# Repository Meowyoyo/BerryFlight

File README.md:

# BerryFlight
A UAV flight controller with advanced video and computing capabilities.

BerryFlight is a flight control board based on established BetaFlight / INAV Flight STM32 flifgt controllers. 

In addition to that it brings a RV1126 ARM Quadcore SoC, 2 GB of RAM and 8 GB of storage.
The on board Linux will propell you UAV into the next century =D

Running OpenHD with a USB Cam or use the two analog video inputs. 
Send the video digital over Wifibroadcast or analog via a normal 5.8 GHz VTX.

## The specs:
- STM32F722RET (BF/INAV/Ardu?) based flight controller
- 36x36mm 6-layer board, 30.5mm mounting holes
- ICM-20602 gyro
- BME280 baro
- Rockchip RV1126 ARM quadcore Cortex-A7 
- 2GB LPDDR3 RAM
- 8GB eMMC storage
- analog video out
- USB 2.0 and USB 3.0
- TVP5150AM1 analog video in IC, 2 channel
- AXP805 power management IC, 5 channel DC-DC, 10 channel LDO

## Contact:
Any additional functions needed?
Feel free to improve my design.
Open to any kind of input!

[Telegram Group](https://t.me/joinchat/x0q7eM5X5ahhNjhi)

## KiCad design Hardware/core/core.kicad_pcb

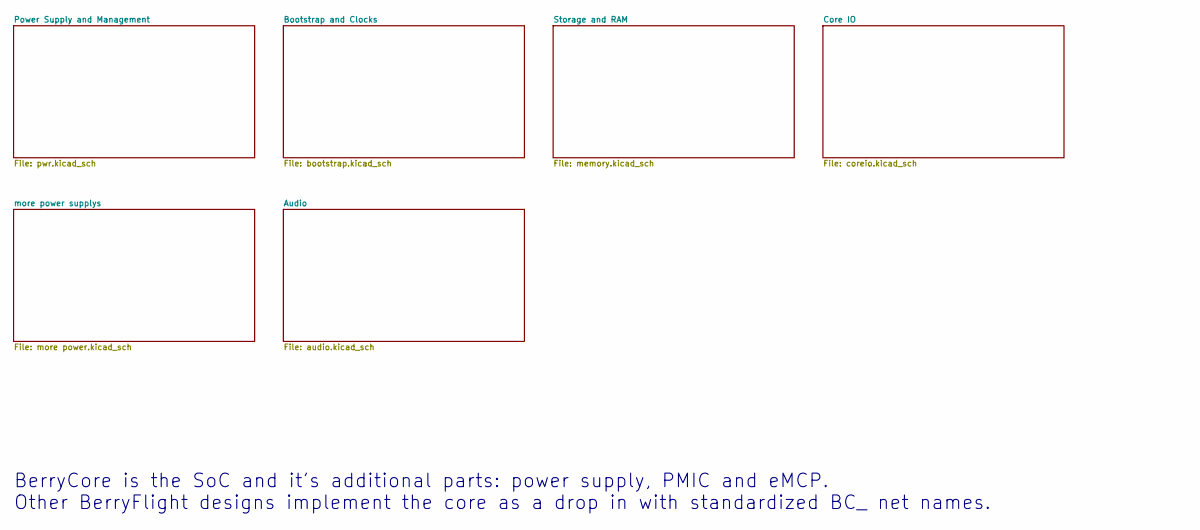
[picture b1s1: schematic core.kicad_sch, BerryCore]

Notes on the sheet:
BerryCore is the SoC and it's additional parts: power supply, PMIC and eMCP. Other BerryFlight designs implement the core as a drop in with standardized BC_ net names.

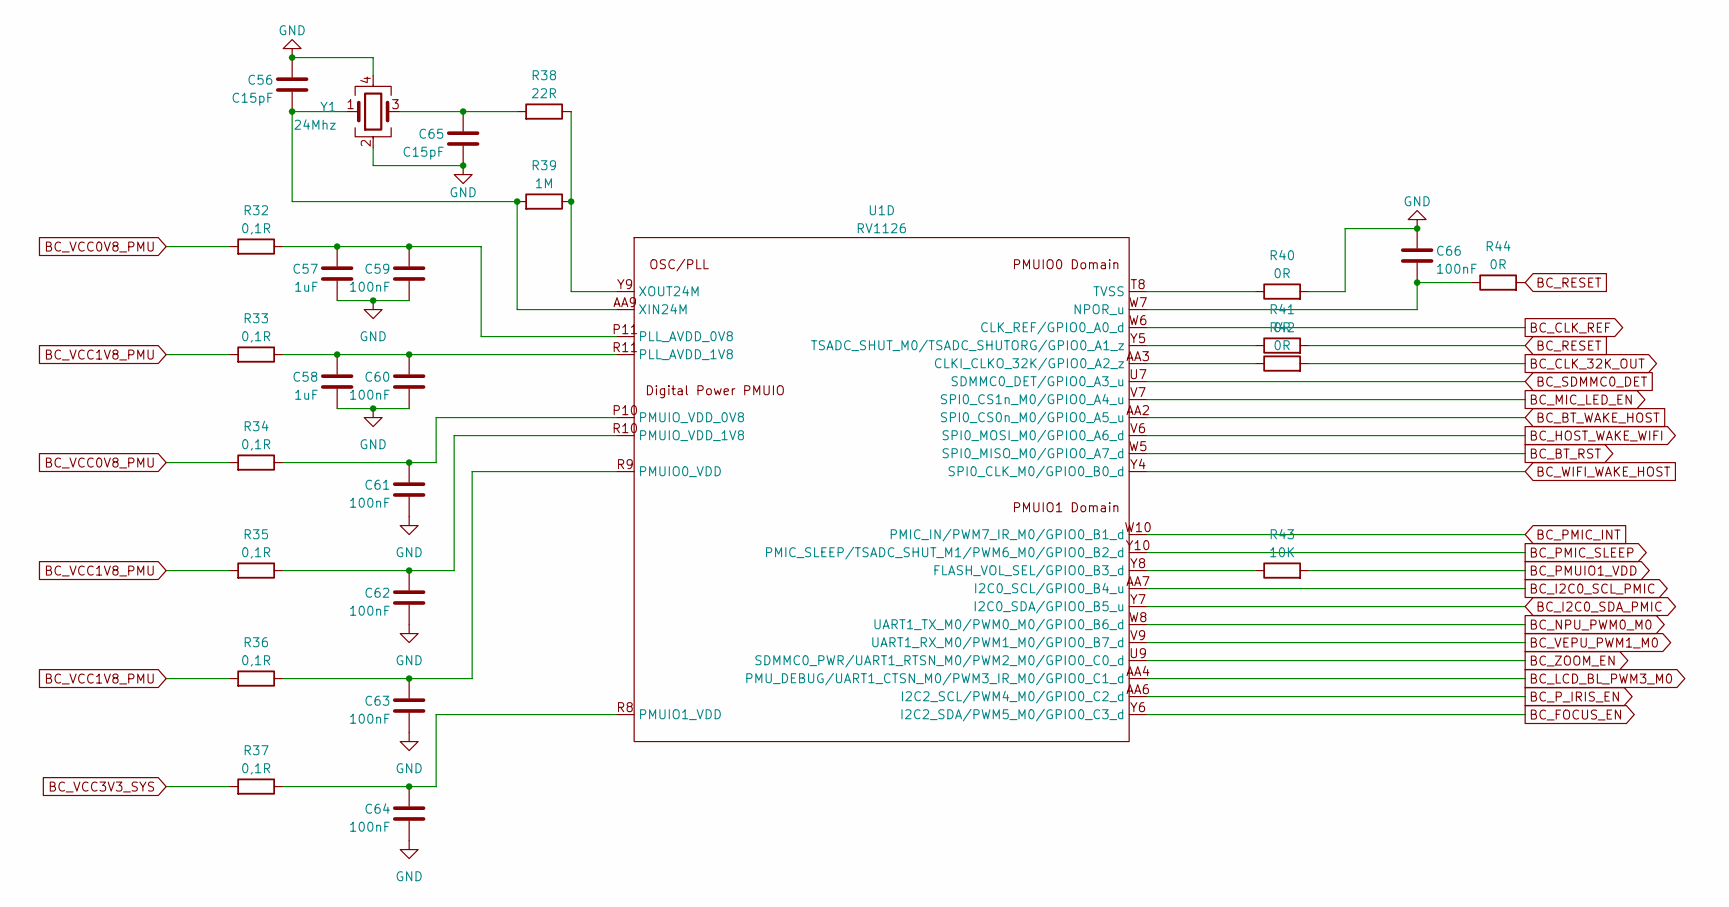
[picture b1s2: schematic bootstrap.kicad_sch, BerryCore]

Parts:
C56, C65: C15pF; C_0402_1005Metric
C57, C58: 1uF; C_0402_1005Metric
C59, C60, C61, C62, C63, C64: 100nF; C_0201_0603Metric
C66: 100nF; C_0402_1005Metric
R32, R33, R34, R35, R36, R37: 0,1R; R_0603_1608Metric
R38: 22R; R_0402_1005Metric
R39: 1M; R_0402_1005Metric
R40, R41, R42, R44: 0R; R_0402_1005Metric
R43: 10K; R_0402_1005Metric
U1: RV1126
Y1: 24Mhz; Oscillator_SMD_Abracon_ASE-4Pin_3.2x2.5mm

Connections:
BC_BT_RST: U1.W5 (SPI0_MISO_M0/GPIO0_A7_d)
BC_BT_WAKE_HOST: U1.AA2 (SPI0_CS0n_M0/GPIO0_A5_u)
BC_CLK_32K_OUT: R42.2; also elsewhere on the board
BC_CLK_REF: U1.W6 (CLK_REF/GPIO0_A0_d)
BC_FOCUS_EN: U1.Y6 (I2C2_SDA/PWM5_M0/GPIO0_C3_d)
BC_HOST_WAKE_WIFI: U1.V6 (SPI0_MOSI_M0/GPIO0_A6_d)
BC_I2C0_SCL_PMIC: U1.AA7 (I2C0_SCL/GPIO0_B4_u); also elsewhere on the board
BC_I2C0_SDA_PMIC: U1.Y7 (I2C0_SDA/GPIO0_B5_u); also elsewhere on the board
BC_LCD_BL_PWM3_M0: U1.AA4 (PMU_DEBUG/UART1_CTSN_M0/PWM3_IR_M0/GPIO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)
BC_MIC_LED_EN: U1.V7 (SPI0_CS1n_M0/GPIO0_A4_u)
BC_NPU_PWM0_M0: U1.W8 (UART1_TX_M0/PWM0_M0/GPIO0_B6_d); also elsewhere on the board
BC_PMIC_INT: U1.W10 (PMIC_IN/PWM7_IR_M0/GPIO0_B1_d); also elsewhere on the board
BC_PMIC_SLEEP: U1.Y10 (PMIC_SLEEP/TSADC_SHUT_M1/PWM6_M0/GPIO0_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); also elsewhere on the board
BC_PMUIO1_VDD: R43.2
BC_P_IRIS_EN: U1.AA6 (I2C2_SCL/PWM4_M0/GPIO0_C2_d)
BC_RESET: R41.2, R44.2; also elsewhere on the board
BC_SDMMC0_DET: U1.U7 (SDMMC0_DET/GPIO0_A3_u)
BC_VCC0V8_PMU: R32.2, R34.2; also elsewhere on the board
BC_VCC1V8_PMU: R33.2, R35.2, R36.2; also elsewhere on the board
BC_VCC3V3_SYS: R37.2; also elsewhere on the board
BC_VEPU_PWM1_M0: U1.V9 (UART1_RX_M0/PWM1_M0/GPIO0_B7_d)
BC_WIFI_WAKE_HOST: U1.Y4 (SPI0_CLK_M0/GPIO0_B0_d)
BC_ZOOM_EN: U1.U9 (SDMMC0_PWR/UART1_RTSN_M0/PWM2_M0/GPIO0_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)
GND: C56.1, C57.2, C58.2, C59.2, C60.2, C61.2, C62.2, C63.2, C64.2, C65.2, C66.1, R40.2, Y1.2, Y1.4; also elsewhere on the board
unnamed: C56.2, R39.2, U1.AA9 (XIN24M), Y1.1
unnamed: C57.1, C59.1, R32.1, U1.P11 (PLL_AVDD_0V8)
unnamed: C58.1, C60.1, R33.1, U1.R11 (PLL_AVDD_1V8)
unnamed: C61.1, R34.1, U1.P10 (PMUIO_VDD_0V8)
unnamed: C62.1, R35.1, U1.R10 (PMUIO_VDD_1V8)
unnamed: C63.1, R36.1, U1.R9 (PMUIO0_VDD)
unnamed: C64.1, R37.1, U1.R8 (PMUIO1_VDD)
unnamed: C65.1, R38.2, Y1.3
unnamed: C66.2, R44.1, U1.W7 (NPOR_u)
unnamed: R38.1, R39.1, U1.Y9 (XOUT24M)
unnamed: R40.1, U1.T8 (TVSS)
unnamed: R41.1, U1.Y5 (TSADC_SHUT_M0/TSADC_SHUTORG/GPIO0_A1_z)
unnamed: R42.1, U1.AA3 (CLKI_CLKO_32K/GPIO0_A2_z)
unnamed: R43.1, U1.Y8 (FLASH_VOL_SEL/GPIO0_B3_d)

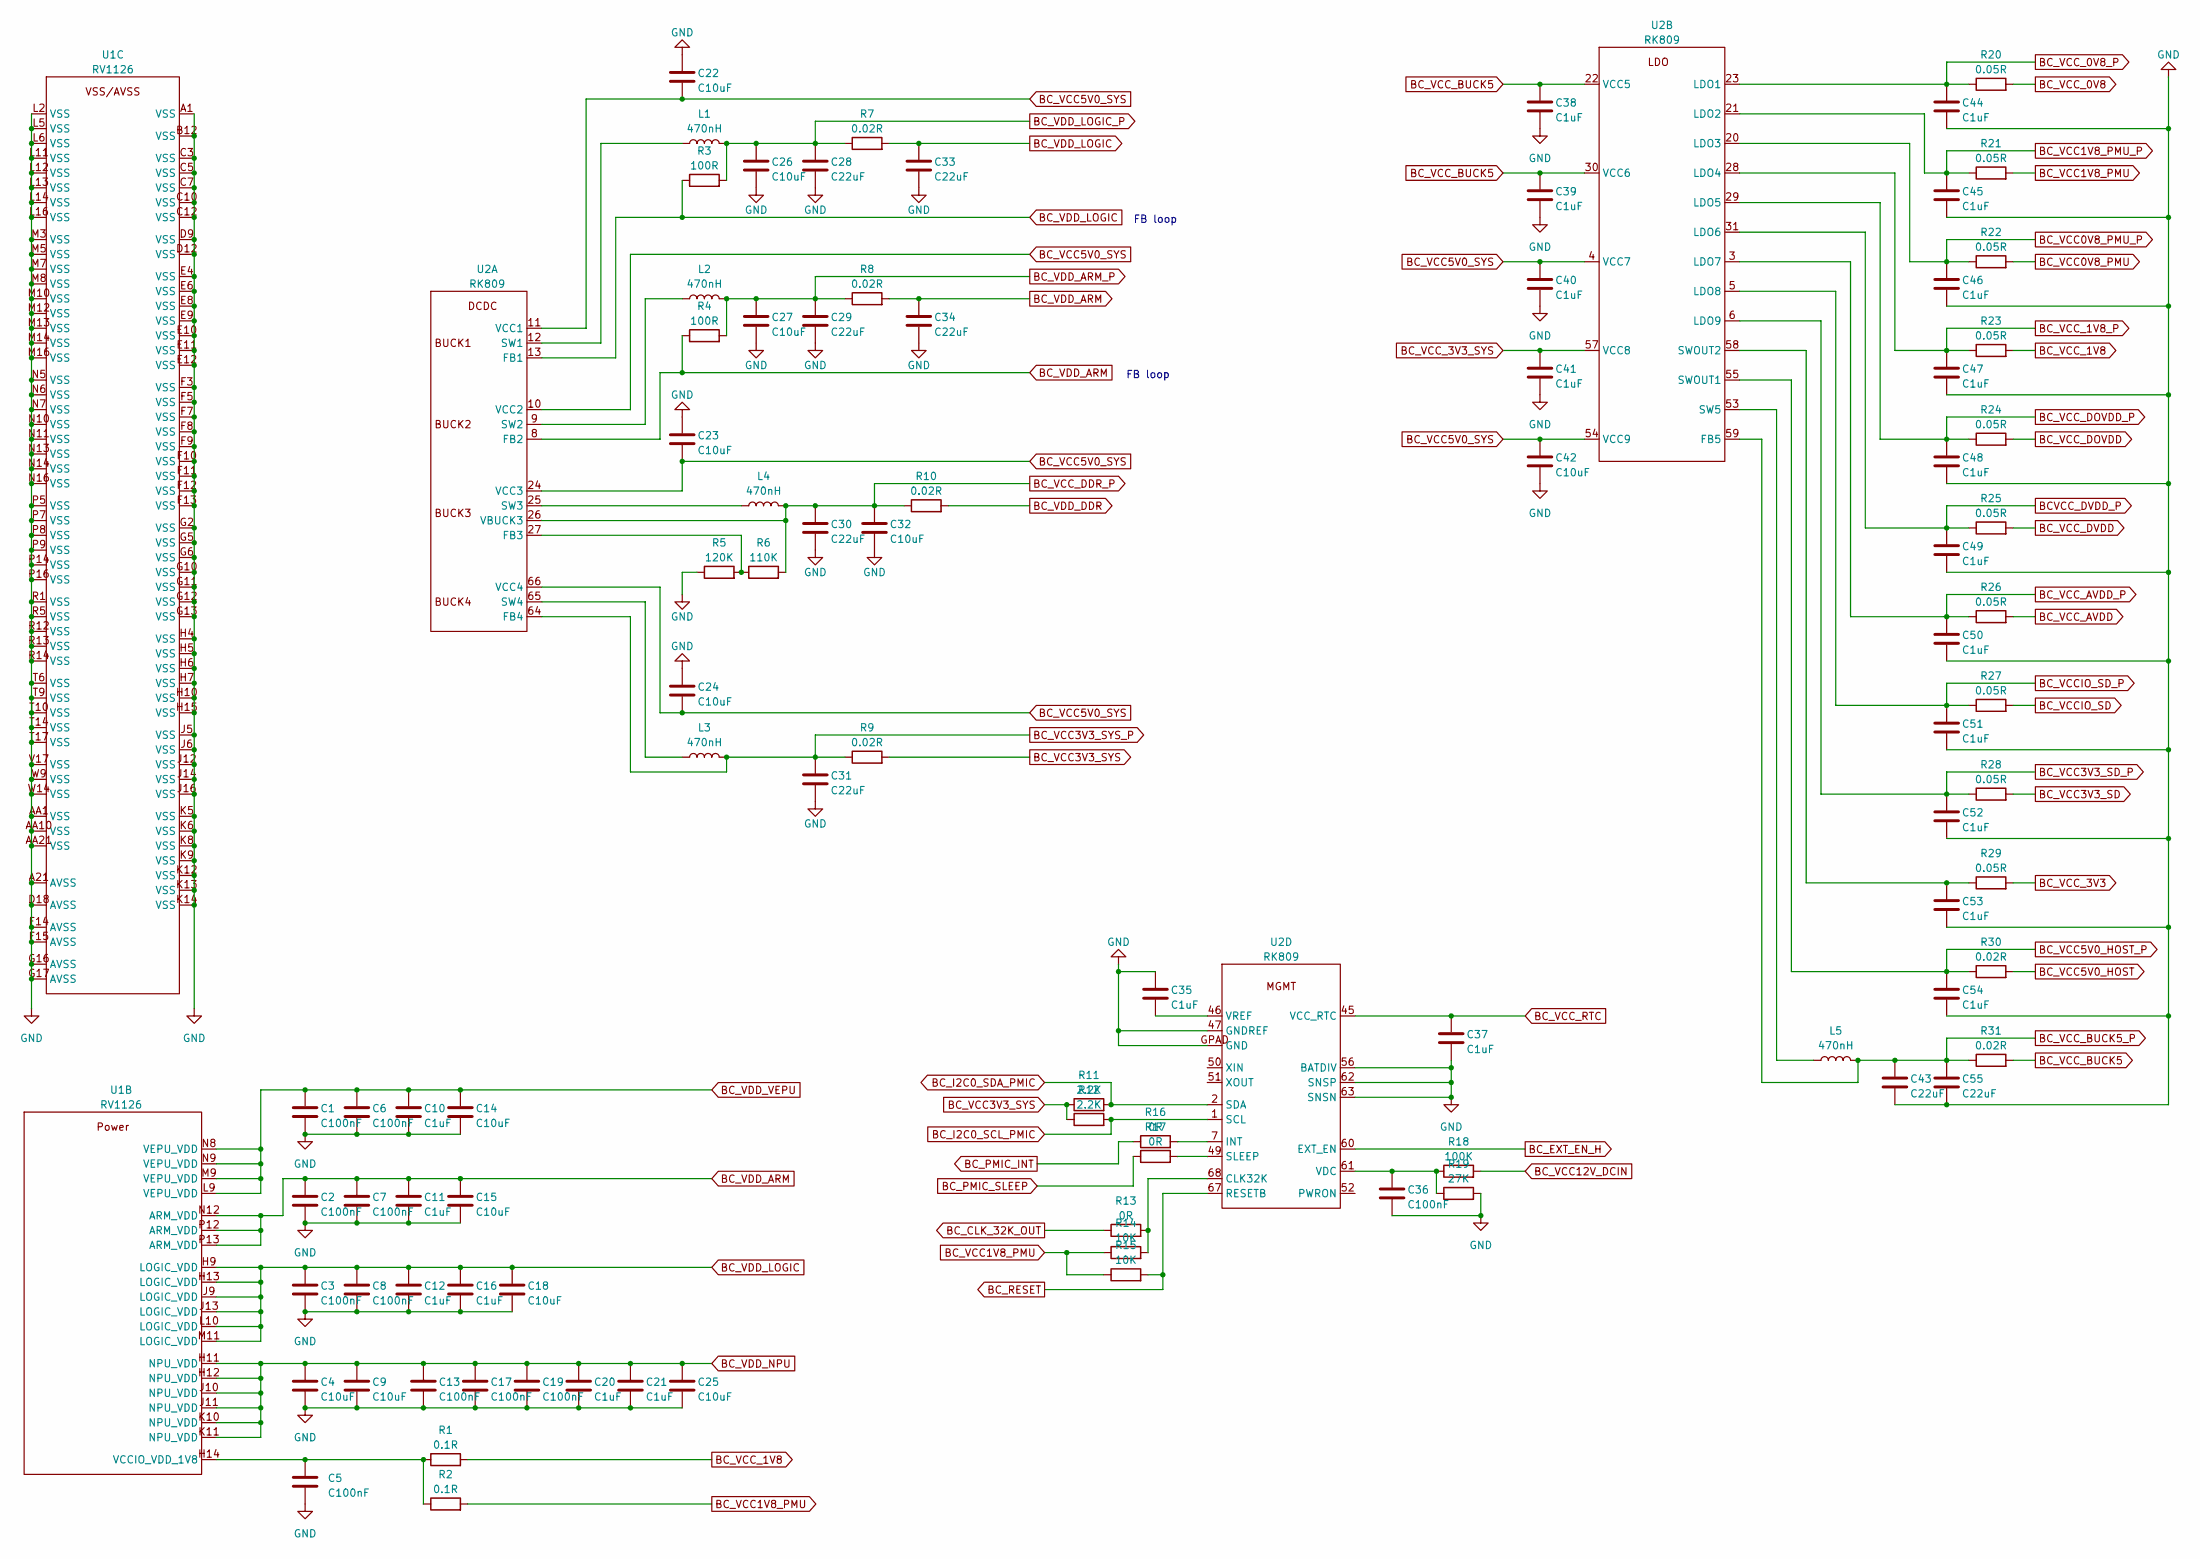
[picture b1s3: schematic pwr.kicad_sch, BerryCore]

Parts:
C1, C2, C3, C6, C7, C8, C13, C17, C19: C100nF; C_0201_0603Metric
C4, C9, C22, C23, C24, C26, C27, C32, C42: C10uF; C_0603_1608Metric
C5, C36: C100nF; C_0402_1005Metric
C10, C11, C12, C16, C20, C21, C35, C37, C38, C39, C40, C41, C44, C45, C46, C47, C48, C49, C50, C51, C52, C53, C54: C1uF; C_0402_1005Metric
C14, C15, C18, C25: C10uF; C_0402_1005Metric
C28, C29, C30, C31, C33, C34, C43, C55: C22uF; C_0603_1608Metric
L1, L2, L3, L4, L5: 470nH; L_1008_2520Metric
R1, R2: 0.1R; R_0603_1608Metric
R3, R4: 100R; R_0402_1005Metric
R5: 120K; R_0402_1005Metric
R6: 110K; R_0402_1005Metric
R7, R8, R9, R10, R30, R31: 0.02R; R_0805_2012Metric
R11, R12: 2.2K; R_0402_1005Metric
R13, R16, R17: 0R; R_0402_1005Metric
R14, R15: 10K; R_0402_1005Metric
R18: 100K; R_0402_1005Metric
R19: 27K; R_0402_1005Metric
R20, R21, R22, R23, R24, R25, R26, R27, R28, R29: 0.05R; R_0603_1608Metric
U1: RV1126
U2: RK809; QFN-68_EP_7x7_Pitch0.35mm

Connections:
BCVCC_DVDD_P: C49.1, R25.1, U2.31 (LDO6)
BC_CLK_32K_OUT: R13.1; also elsewhere on the board
BC_EXT_EN_H: U2.60 (EXT_EN); also elsewhere on the board
BC_I2C0_SCL_PMIC: R12.2, U2.1 (SCL); also elsewhere on the board
BC_I2C0_SDA_PMIC: R11.2, U2.2 (SDA); also elsewhere on the board
BC_PMIC_INT: R16.1; also elsewhere on the board
BC_PMIC_SLEEP: R17.1; also elsewhere on the board
BC_RESET: R15.2, U2.67 (RESETB); also elsewhere on the board
BC_VCC0V8_PMU: R22.2; also elsewhere on the board
BC_VCC0V8_PMU_P: C46.1, R22.1, U2.20 (LDO3)
BC_VCC1V8_PMU: R2.2, R14.1, R15.1, R21.2; also elsewhere on the board
BC_VCC1V8_PMU_P: C45.1, R21.1, U2.21 (LDO2)
BC_VCC3V3_SD: R28.2
BC_VCC3V3_SD_P: C52.1, R28.1, U2.6 (LDO9)
BC_VCC3V3_SYS: R9.2, R11.1, R12.1; also elsewhere on the board
BC_VCC3V3_SYS_P: C31.1, L3.2, R9.1, U2.64 (FB4)
BC_VCC5V0_HOST: R30.2
BC_VCC5V0_HOST_P: C54.1, R30.1, U2.55 (SWOUT1)
BC_VCC5V0_SYS: C22.2, C23.2, C24.2, C40.1, C42.1, U2.4 (VCC7), U2.10 (VCC2), U2.11 (VCC1), U2.24 (VCC3), U2.54 (VCC9), U2.66 (VCC4); also elsewhere on the board
BC_VCC12V_DCIN: R18.2
BC_VCCIO_SD: R27.2
BC_VCCIO_SD_P: C51.1, R27.1, U2.5 (LDO8)
BC_VCC_0V8: R20.2
BC_VCC_0V8_P: C44.1, R20.1, U2.23 (LDO1)
BC_VCC_1V8: R1.2, R23.2
BC_VCC_1V8_P: C47.1, R23.1, U2.28 (LDO4)
BC_VCC_3V3: R29.2; also elsewhere on the board
BC_VCC_3V3_SYS: C41.1, U2.57 (VCC8)
BC_VCC_AVDD: R26.2
BC_VCC_AVDD_P: C50.1, R26.1, U2.3 (LDO7)
BC_VCC_BUCK5: C38.1, C39.1, R31.2, U2.22 (VCC5), U2.30 (VCC6)
BC_VCC_BUCK5_P: C43.1, C55.1, L5.2, R31.1, U2.59 (FB5)
BC_VCC_DDR_P: C30.1, C32.1, L4.2, R6.2, R10.1, U2.26 (VBUCK3)
BC_VCC_DOVDD: R24.2
BC_VCC_DOVDD_P: C48.1, R24.1, U2.29 (LDO5)
BC_VCC_DVDD: R25.2
BC_VCC_RTC: C37.1, U2.45 (VCC_RTC); also elsewhere on the board
BC_VDD_ARM: C2.1, C7.1, C11.1, C15.1, C34.1, R4.1, R8.2, U1.N12 (ARM_VDD), U1.P12 (ARM_VDD), U1.P13 (ARM_VDD), U2.8 (FB2); also elsewhere on the board
BC_VDD_ARM_P: C27.1, C29.1, L2.2, R4.2, R8.1
BC_VDD_DDR: R10.2
BC_VDD_LOGIC: C3.1, C8.1, C12.1, C16.1, C18.1, C33.1, R3.1, R7.2, U1.H9 (LOGIC_VDD), U1.H13 (LOGIC_VDD), U1.J9 (LOGIC_VDD), U1.J13 (LOGIC_VDD), U1.L10 (LOGIC_VDD), U1.M11 (LOGIC_VDD), U2.13 (FB1)
BC_VDD_LOGIC_P: C26.1, C28.1, L1.2, R3.2, R7.1
BC_VDD_NPU: C4.1, C9.1, C13.1, C17.1, C19.1, C20.1, C21.1, C25.1, U1.H11 (NPU_VDD), U1.H12 (NPU_VDD), U1.J10 (NPU_VDD), U1.J11 (NPU_VDD), U1.K10 (NPU_VDD), U1.K11 (NPU_VDD); also elsewhere on the board
BC_VDD_VEPU: C1.1, C6.1, C10.1, C14.1, U1.L9 (VEPU_VDD), U1.M9 (VEPU_VDD), U1.N8 (VEPU_VDD), U1.N9 (VEPU_VDD); also elsewhere on the board
GND: C1.2, C2.2, C3.2, C4.2, C5.2, C6.2, C7.2, C8.2, C9.2, C10.2, C11.2, C12.2, C13.2, C14.2, C15.2, C16.2, C17.2, C18.2, C19.2, C20.2, C21.2, C22.1, C23.1, C24.1, C25.2, C26.2, C27.2, C28.2, C29.2, C30.2, C31.2, C32.2, C33.2, C34.2, C35.1, C36.2, C37.2, C38.2, C39.2, C40.2, C41.2, C42.2, C43.2, C44.2, C45.2, C46.2, C47.2, C48.2, C49.2, C50.2, C51.2, C52.2, C53.2, C54.2, C55.2, R5.1, R19.2, U1.A1 (VSS), U1.A21 (AVSS), U1.AA1 (VSS), U1.AA10 (VSS), U1.AA21 (VSS), U1.B12 (VSS), U1.C3 (VSS), U1.C5 (VSS), U1.C7 (VSS), U1.C10 (VSS), U1.C12 (VSS), U1.D9 (VSS), U1.D12 (VSS), U1.D18 (AVSS), U1.E4 (VSS), U1.E6 (VSS), U1.E8 (VSS), U1.E9 (VSS), U1.E10 (VSS), U1.E11 (VSS), U1.E12 (VSS), U1.F3 (VSS), U1.F5 (VSS), U1.F7 (VSS), U1.F8 (VSS), U1.F9 (VSS), U1.F10 (VSS), U1.F11 (VSS), U1.F12 (VSS), U1.F13 (VSS), U1.F14 (AVSS), U1.F15 (AVSS), U1.G2 (VSS), U1.G5 (VSS), U1.G6 (VSS), U1.G10 (VSS), U1.G11 (VSS), U1.G12 (VSS), U1.G13 (VSS), U1.G16 (AVSS), U1.G17 (AVSS), U1.H4 (VSS), U1.H5 (VSS), U1.H6 (VSS), U1.H7 (VSS), U1.H10 (VSS), U1.H15 (VSS), U1.J5 (VSS), U1.J6 (VSS), U1.J12 (VSS), U1.J14 (VSS), U1.J16 (VSS), U1.K5 (VSS), U1.K6 (VSS), U1.K8 (VSS), U1.K9 (VSS), U1.K12 (VSS), U1.K13 (VSS), U1.K14 (VSS), U1.L2 (VSS), U1.L5 (VSS), U1.L6 (VSS), U1.L11 (VSS), U1.L12 (VSS), U1.L13 (VSS), U1.L14 (VSS), U1.L16 (VSS), U1.M3 (VSS), U1.M5 (VSS), U1.M7 (VSS), U1.M8 (VSS), U1.M10 (VSS), U1.M12 (VSS), U1.M13 (VSS), U1.M14 (VSS), U1.M16 (VSS), U1.N5 (VSS), U1.N6 (VSS), U1.N7 (VSS), U1.N10 (VSS), U1.N11 (VSS), U1.N13 (VSS), U1.N14 (VSS), U1.N16 (VSS), U1.P5 (VSS), U1.P7 (VSS), U1.P8 (VSS), U1.P9 (VSS), U1.P14 (VSS), U1.P16 (VSS), U1.R1 (VSS), U1.R5 (VSS), U1.R12 (VSS), U1.R13 (VSS), U1.R14 (VSS), U1.T6 (VSS), U1.T9 (VSS), U1.T10 (VSS), U1.T14 (VSS), U1.T17 (VSS), U1.V17 (VSS), U1.W9 (VSS), U1.W14 (VSS), U2.47 (GNDREF), U2.56 (BATDIV), U2.62 (SNSP), U2.63 (SNSN), U2.GPAD (GND); also elsewhere on the board
unnamed: C5.1, R1.1, R2.1, U1.H14 (VCCIO_VDD_1V8)
unnamed: C35.2, U2.46 (VREF)
unnamed: C36.1, R18.1, R19.1, U2.61 (VDC)
unnamed: C53.1, R29.1, U2.58 (SWOUT2)
unnamed: L1.1, U2.12 (SW1)
unnamed: L2.1, U2.9 (SW2)
unnamed: L3.1, U2.65 (SW4)
unnamed: L4.1, U2.25 (SW3)
unnamed: L5.1, U2.53 (SW5)
unnamed: R5.2, R6.1, U2.27 (FB3)
unnamed: R13.2, R14.2, U2.68 (CLK32K)
unnamed: R16.2, U2.7 (INT)
unnamed: R17.2, U2.49 (SLEEP)

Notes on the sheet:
FB loop

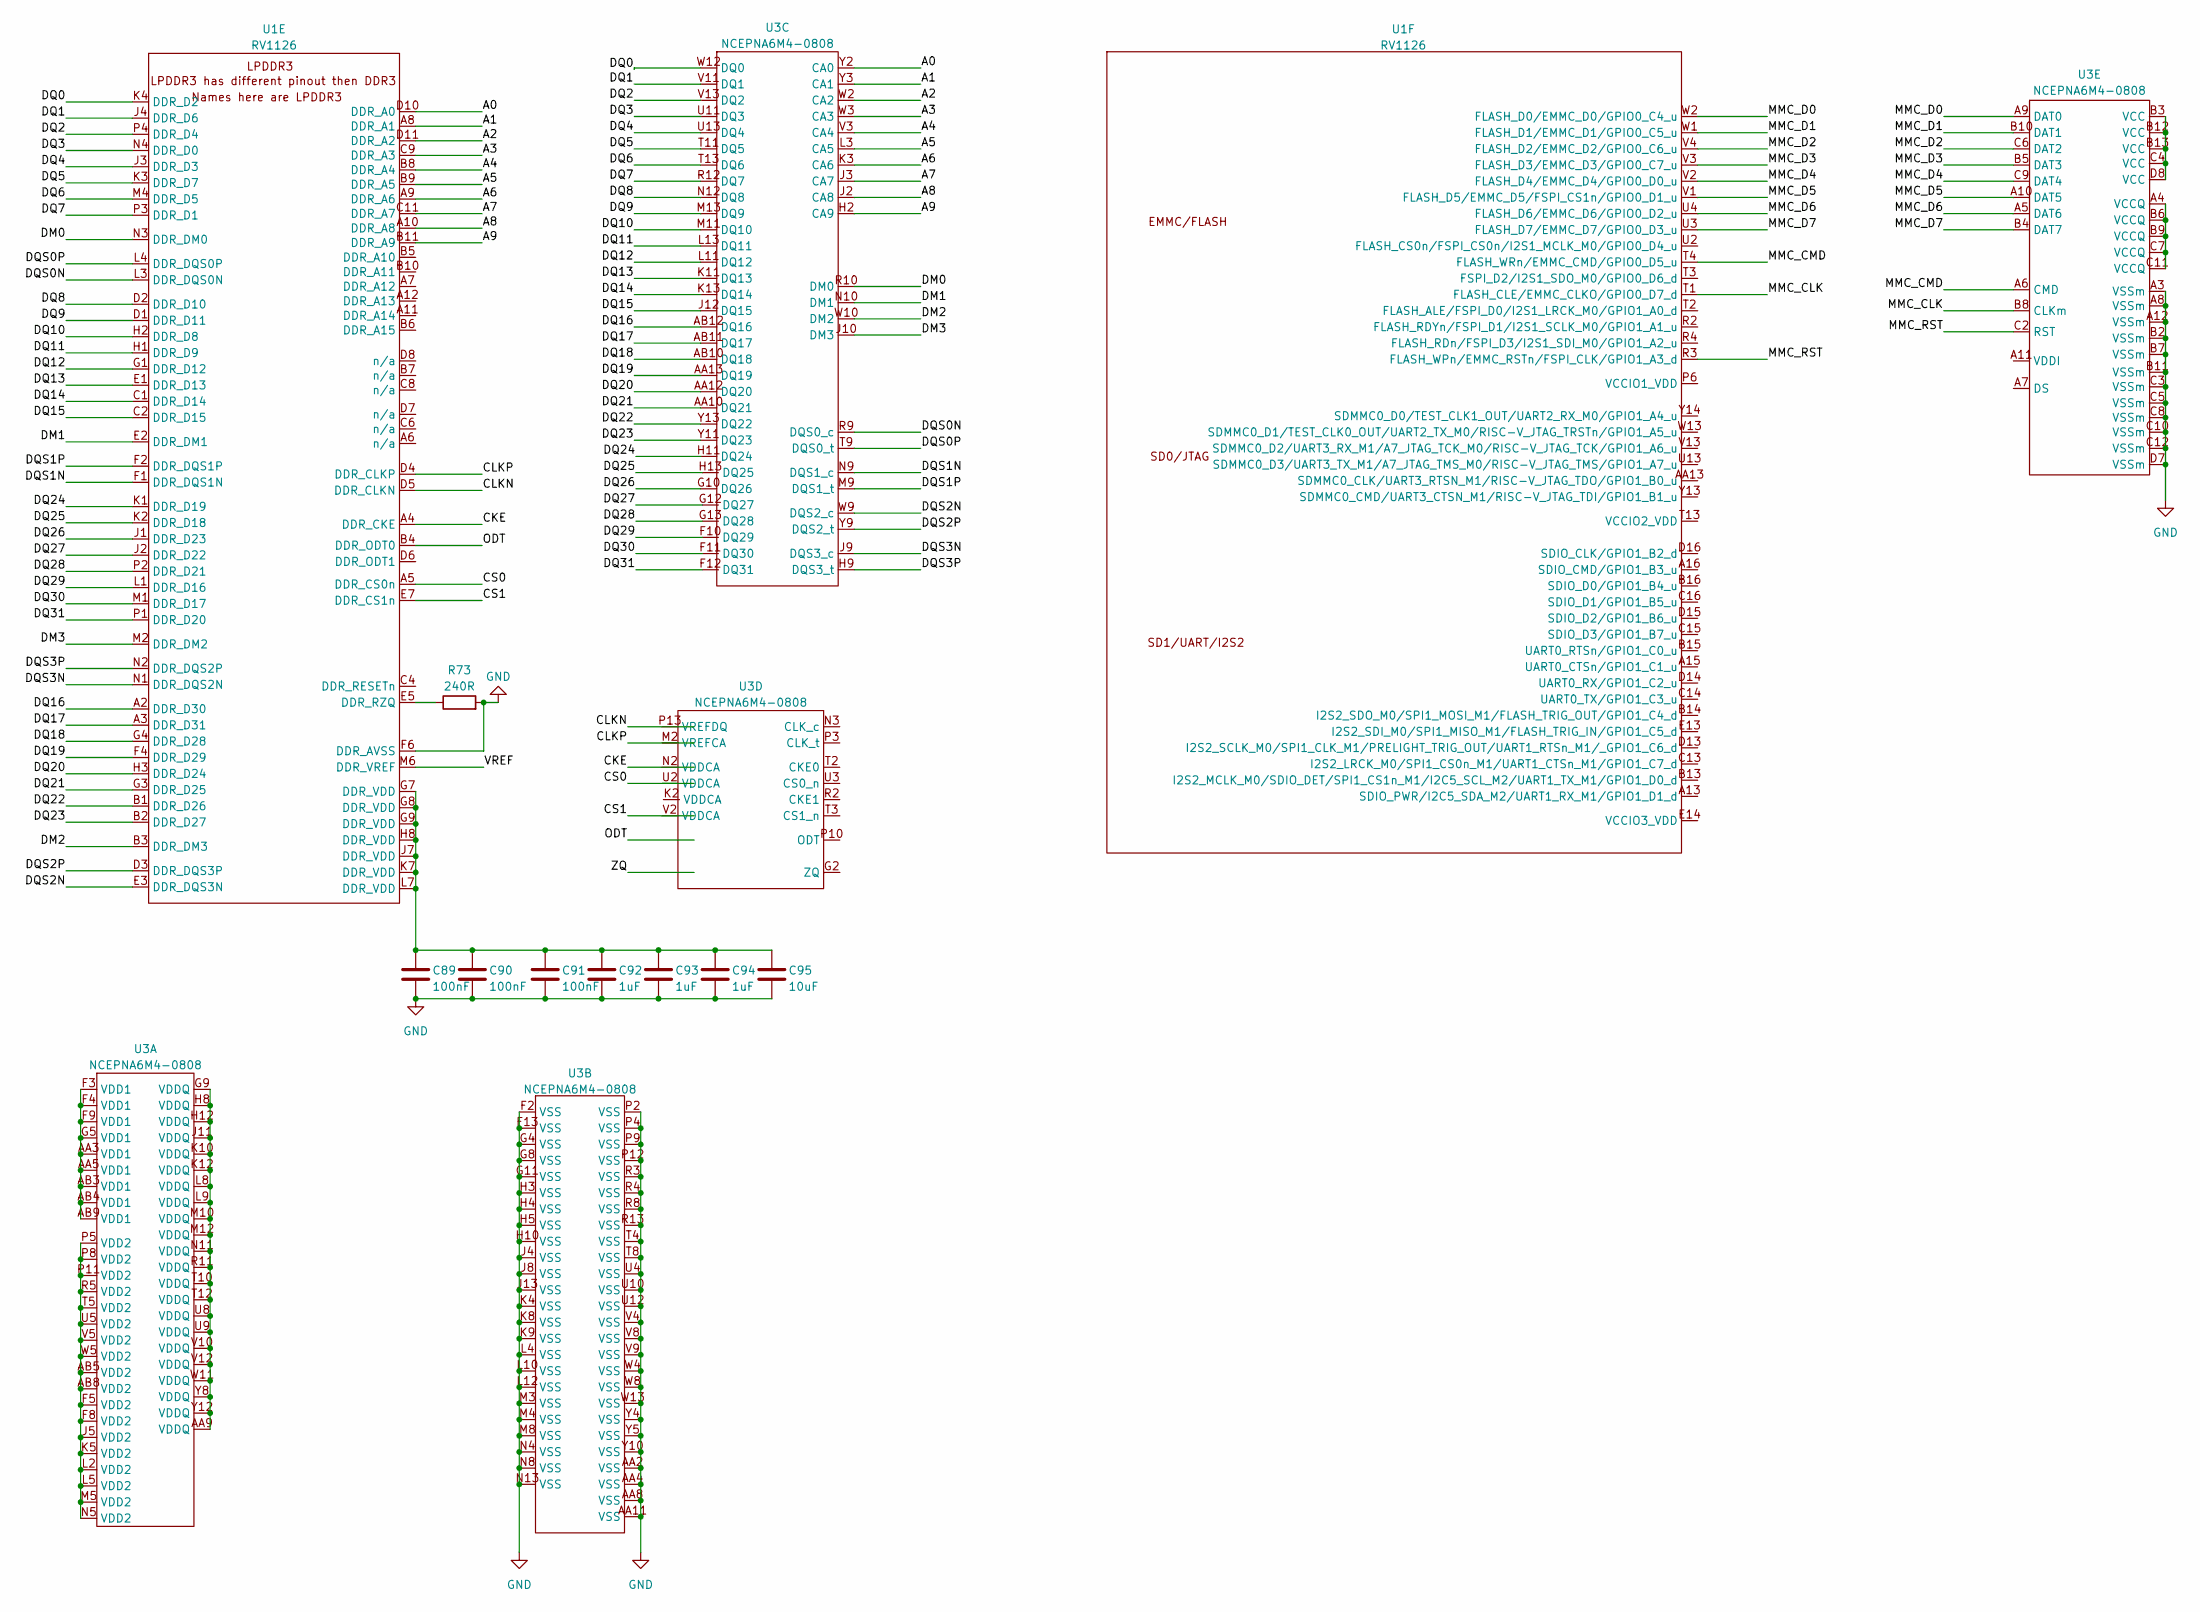
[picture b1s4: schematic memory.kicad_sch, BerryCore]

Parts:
C89, C90, C91: 100nF; C_0201_0603Metric
C92, C93, C94: 1uF; C_0402_1005Metric
C95: 10uF; C_0603_1608Metric
R73: 240R; R_0402_1005Metric
U1: RV1126
U3: NCEPNA6M4-0808; BGA-221

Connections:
/Storage and RAM/A0: U1.D10 (DDR_A0), U3.Y2 (CA0)
/Storage and RAM/A1: U1.A8 (DDR_A1), U3.Y3 (CA1)
/Storage and RAM/A2: U1.D11 (DDR_A2), U3.W2 (CA2)
/Storage and RAM/A3: U1.C9 (DDR_A3), U3.W3 (CA3)
/Storage and RAM/A4: U1.B8 (DDR_A4), U3.V3 (CA4)
/Storage and RAM/A5: U1.B9 (DDR_A5), U3.L3 (CA5)
/Storage and RAM/A6: U1.A9 (DDR_A6), U3.K3 (CA6)
/Storage and RAM/A7: U1.C11 (DDR_A7), U3.J3 (CA7)
/Storage and RAM/A8: U1.A10 (DDR_A8), U3.J2 (CA8)
/Storage and RAM/A9: U1.B11 (DDR_A9), U3.H2 (CA9)
/Storage and RAM/CKE: U1.A4 (DDR_CKE), U3.T2 (CKE0)
/Storage and RAM/CLKN: U1.D5 (DDR_CLKN), U3.N3 (CLK_c)
/Storage and RAM/CLKP: U1.D4 (DDR_CLKP), U3.P3 (CLK_t)
/Storage and RAM/CS0: U1.A5 (DDR_CS0n), U3.U3 (CS0_n)
/Storage and RAM/CS1: U1.E7 (DDR_CS1n), U3.T3 (CS1_n)
/Storage and RAM/DM1: U1.E2 (DDR_DM1), U3.N10 (DM1)
/Storage and RAM/DM2: U1.B3 (DDR_DM3), U3.W10 (DM2)
/Storage and RAM/DM3: U1.M2 (DDR_DM2), U3.J10 (DM3)
/Storage and RAM/DQ0: U1.K4 (DDR_D2), U3.W12 (DQ0)
/Storage and RAM/DQ1: U1.J4 (DDR_D6), U3.V11 (DQ1)
/Storage and RAM/DQ2: U1.P4 (DDR_D4), U3.V13 (DQ2)
/Storage and RAM/DQ3: U1.N4 (DDR_D0), U3.U11 (DQ3)
/Storage and RAM/DQ4: U1.J3 (DDR_D3), U3.U13 (DQ4)
/Storage and RAM/DQ5: U1.K3 (DDR_D7), U3.T11 (DQ5)
/Storage and RAM/DQ7: U1.P3 (DDR_D1), U3.R12 (DQ7)
/Storage and RAM/DQ8: U1.D2 (DDR_D10), U3.N12 (DQ8)
/Storage and RAM/DQ9: U1.D1 (DDR_D11), U3.M13 (DQ9)
/Storage and RAM/DQ10: U1.H2 (DDR_D8), U3.M11 (DQ10)
/Storage and RAM/DQ11: U1.H1 (DDR_D9), U3.L13 (DQ11)
/Storage and RAM/DQ12: U1.G1 (DDR_D12), U3.L11 (DQ12)
/Storage and RAM/DQ13: U1.E1 (DDR_D13), U3.K11 (DQ13)
/Storage and RAM/DQ14: U1.C1 (DDR_D14), U3.K13 (DQ14)
/Storage and RAM/DQ15: U1.C2 (DDR_D15), U3.J12 (DQ15)
/Storage and RAM/DQ16: U1.A2 (DDR_D30), U3.AB12 (DQ16)
/Storage and RAM/DQ17: U1.A3 (DDR_D31), U3.AB11 (DQ17)
/Storage and RAM/DQ18: U1.G4 (DDR_D28), U3.AB10 (DQ18)
/Storage and RAM/DQ19: U1.F4 (DDR_D29), U3.AA13 (DQ19)
/Storage and RAM/DQ20: U1.H3 (DDR_D24), U3.AA12 (DQ20)
/Storage and RAM/DQ21: U1.G3 (DDR_D25), U3.AA10 (DQ21)
/Storage and RAM/DQ22: U1.B1 (DDR_D26), U3.Y13 (DQ22)
/Storage and RAM/DQ23: U1.B2 (DDR_D27), U3.Y11 (DQ23)
/Storage and RAM/DQ24: U1.K1 (DDR_D19), U3.H11 (DQ24)
/Storage and RAM/DQ25: U1.K2 (DDR_D18), U3.H13 (DQ25)
/Storage and RAM/DQ26: U1.J1 (DDR_D23), U3.G10 (DQ26)
/Storage and RAM/DQ27: U1.J2 (DDR_D22), U3.G12 (DQ27)
/Storage and RAM/DQ28: U1.P2 (DDR_D21), U3.G13 (DQ28)
/Storage and RAM/DQ29: U1.L1 (DDR_D16), U3.F10 (DQ29)
/Storage and RAM/DQ30: U1.M1 (DDR_D17), U3.F11 (DQ30)
/Storage and RAM/DQ31: U1.P1 (DDR_D20), U3.F12 (DQ31)
/Storage and RAM/DQS0P: U1.L4 (DDR_DQS0P), U3.T9 (DQS0_t)
/Storage and RAM/DQS1N: U1.F1 (DDR_DQS1N), U3.N9 (DQS1_c)
/Storage and RAM/DQS1P: U1.F2 (DDR_DQS1P), U3.M9 (DQS1_t)
/Storage and RAM/DQS2N: U1.E3 (DDR_DQS3N), U3.W9 (DQS2_c)
/Storage and RAM/DQS2P: U1.D3 (DDR_DQS3P), U3.Y9 (DQS2_t)
/Storage and RAM/DQS3N: U1.N1 (DDR_DQS2N), U3.J9 (DQS3_c)
/Storage and RAM/DQS3P: U1.N2 (DDR_DQS2P), U3.H9 (DQS3_t)
/Storage and RAM/MMC_CLK: U1.T1 (FLASH_CLE/EMMC_CLKO/GPIO0_D7_d), U3.B8 (CLKm)
/Storage and RAM/MMC_CMD: U1.T4 (FLASH_WRn/EMMC_CMD/GPIO0_D5_u), U3.A6 (CMD)
/Storage and RAM/MMC_D0: U1.W2 (FLASH_D0/EMMC_D0/GPIO0_C4_u), U3.A9 (DAT0)
/Storage and RAM/MMC_D1: U1.W1 (FLASH_D1/EMMC_D1/GPIO0_C5_u), U3.B10 (DAT1)
/Storage and RAM/MMC_D2: U1.V4 (FLASH_D2/EMMC_D2/GPIO0_C6_u), U3.C6 (DAT2)
/Storage and RAM/MMC_D3: U1.V3 (FLASH_D3/EMMC_D3/GPIO0_C7_u), U3.B5 (DAT3)
/Storage and RAM/MMC_D4: U1.V2 (FLASH_D4/EMMC_D4/GPIO0_D0_u), U3.C9 (DAT4)
/Storage and RAM/MMC_D5: U1.V1 (FLASH_D5/EMMC_D5/FSPI_CS1n/GPIO0_D1_u), U3.A10 (DAT5)
/Storage and RAM/MMC_D6: U1.U4 (FLASH_D6/EMMC_D6/GPIO0_D2_u), U3.A5 (DAT6)
/Storage and RAM/MMC_RST: U1.R3 (FLASH_WPn/EMMC_RSTn/FSPI_CLK/GPIO1_A3_d), U3.C2 (RST)
/Storage and RAM/ODT: U1.B4 (DDR_ODT0), U3.P10 (ODT)
/Storage and RAM/VREF: U1.M6 (DDR_VREF)
/Storage and RAM/ZQ: U3.G2 (ZQ)
GND: C89.2, C90.2, C91.2, C92.2, C93.2, C94.2, C95.2, R73.2, U1.F6 (DDR_AVSS), U3.A3 (VSSm), U3.A8 (VSSm), U3.A12 (VSSm), U3.AA2 (VSS), U3.AA4 (VSS), U3.AA8 (VSS), U3.AA11 (VSS), U3.B2 (VSSm), U3.B7 (VSSm), U3.B11 (VSSm), U3.C3 (VSSm), U3.C5 (VSSm), U3.C8 (VSSm), U3.C10 (VSSm), U3.C12 (VSSm), U3.D7 (VSSm), U3.F2 (VSS), U3.F13 (VSS), U3.G4 (VSS), U3.G8 (VSS), U3.G11 (VSS), U3.H3 (VSS), U3.H4 (VSS), U3.H5 (VSS), U3.H10 (VSS), U3.J4 (VSS), U3.J8 (VSS), U3.J13 (VSS), U3.K4 (VSS), U3.K8 (VSS), U3.K9 (VSS), U3.L4 (VSS), U3.L10 (VSS), U3.L12 (VSS), U3.M3 (VSS), U3.M4 (VSS), U3.M8 (VSS), U3.N4 (VSS), U3.N8 (VSS), U3.N13 (VSS), U3.P2 (VSS), U3.P4 (VSS), U3.P9 (VSS), U3.P12 (VSS), U3.R3 (VSS), U3.R4 (VSS), U3.R8 (VSS), U3.R13 (VSS), U3.T4 (VSS), U3.T8 (VSS), U3.U4 (VSS), U3.U10 (VSS), U3.U12 (VSS), U3.V4 (VSS), U3.V8 (VSS), U3.V9 (VSS), U3.W4 (VSS), U3.W8 (VSS), U3.W13 (VSS), U3.Y4 (VSS), U3.Y5 (VSS), U3.Y10 (VSS); also elsewhere on the board
unnamed: C89.1, C90.1, C91.1, C92.1, C93.1, C94.1, C95.1, U1.G7 (DDR_VDD), U1.G8 (DDR_VDD), U1.G9 (DDR_VDD), U1.H8 (DDR_VDD), U1.J7 (DDR_VDD), U1.K7 (DDR_VDD), U1.L7 (DDR_VDD)
unnamed: R73.1, U1.E5 (DDR_RZQ)
unnamed: U3.A4 (VCCQ), U3.B6 (VCCQ), U3.B9 (VCCQ), U3.C7 (VCCQ), U3.C11 (VCCQ)
unnamed: U3.AA3 (VDD1), U3.AA5 (VDD1), U3.AB3 (VDD1), U3.AB4 (VDD1), U3.AB9 (VDD1), U3.F3 (VDD1), U3.F4 (VDD1), U3.F9 (VDD1), U3.G5 (VDD1)
unnamed: U3.AA9 (VDDQ), U3.G9 (VDDQ), U3.H8 (VDDQ), U3.H12 (VDDQ), U3.J11 (VDDQ), U3.K10 (VDDQ), U3.K12 (VDDQ), U3.L8 (VDDQ), U3.L9 (VDDQ), U3.M10 (VDDQ), U3.M12 (VDDQ), U3.N11 (VDDQ), U3.R11 (VDDQ), U3.T10 (VDDQ), U3.T12 (VDDQ), U3.U8 (VDDQ), U3.U9 (VDDQ), U3.V10 (VDDQ), U3.V12 (VDDQ), U3.W11 (VDDQ), U3.Y8 (VDDQ), U3.Y12 (VDDQ)
unnamed: U3.B3 (VCC), U3.B12 (VCC), U3.B13 (VCC), U3.C4 (VCC), U3.D8 (VCC)
unnamed: U3.AB5 (VDD2), U3.AB8 (VDD2), U3.F5 (VDD2), U3.F8 (VDD2), U3.J5 (VDD2), U3.K5 (VDD2), U3.L2 (VDD2), U3.L5 (VDD2), U3.M5 (VDD2), U3.N5 (VDD2), U3.P5 (VDD2), U3.P8 (VDD2), U3.P11 (VDD2), U3.R5 (VDD2), U3.T5 (VDD2), U3.U5 (VDD2), U3.V5 (VDD2), U3.W5 (VDD2)

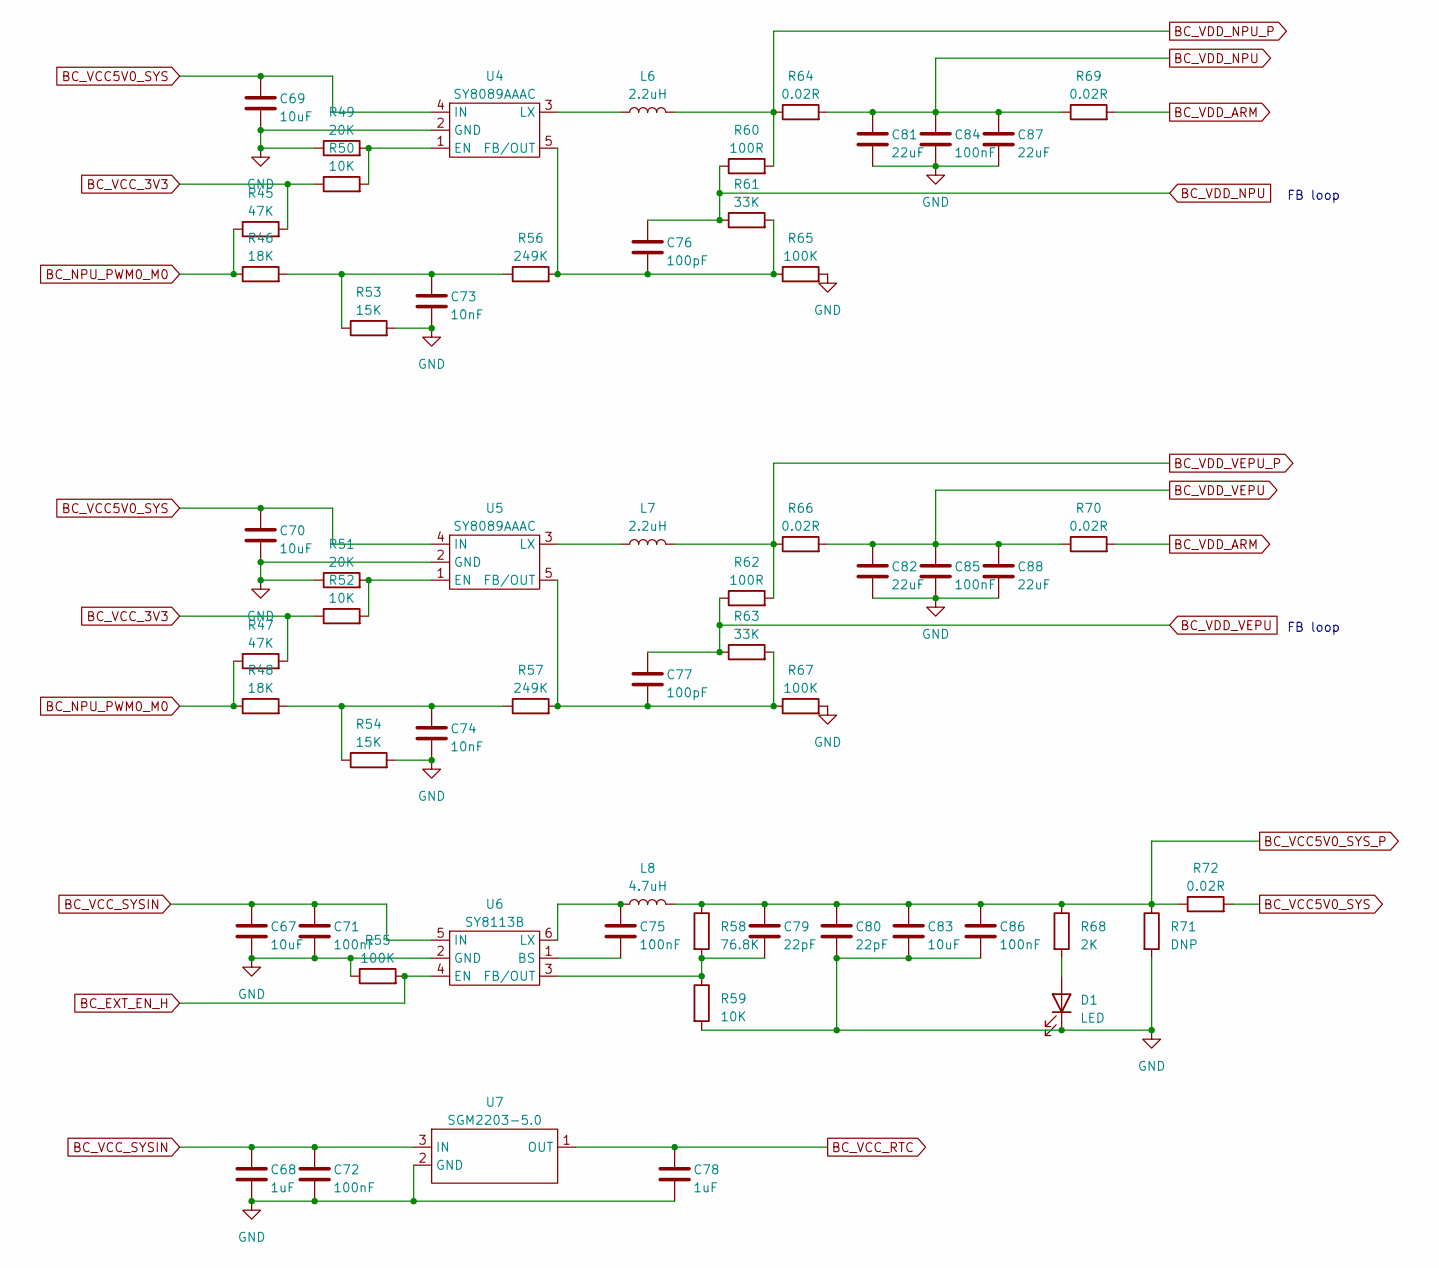
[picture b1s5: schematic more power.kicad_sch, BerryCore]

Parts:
C67, C69, C70, C83: 10uF; C_0805_2012Metric
C68, C78: 1uF; C_0402_1005Metric
C71, C72, C75, C84, C85, C86: 100nF; C_0402_1005Metric
C73, C74: 10nF; C_0402_1005Metric
C76, C77: 100pF; C_0402_1005Metric
C79: 22pF; C_0402_1005Metric
C80: 22pF; C_0805_2012Metric
C81, C82, C87, C88: 22uF; C_0603_1608Metric
D1: LED; LED_0603_1608Metric
L6, L7: 2.2uH; L_1008_2520Metric
L8: 4.7uH; L_TracoPower_TCK-047_5.2x5.8mm
R45, R47: 47K; R_0402_1005Metric
R46, R48: 18K; R_0402_1005Metric
R49, R51: 20K; R_0402_1005Metric
R50, R52, R59: 10K; R_0402_1005Metric
R53, R54: 15K; R_0402_1005Metric
R55, R65, R67: 100K; R_0402_1005Metric
R56, R57: 249K; R_0402_1005Metric
R58: 76.8K; R_0402_1005Metric
R60, R62: 100R; R_0402_1005Metric
R61, R63: 33K; R_0402_1005Metric
R64, R66, R69, R70, R72: 0.02R; R_0805_2012Metric
R68: 2K; R_0402_1005Metric
R71: DNP; R_0402_1005Metric
U4, U5: SY8089AAAC; SOT-23-5
U6: SY8113B; TSOT-23-6
U7: SGM2203-5.0; SOT-23

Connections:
BC_EXT_EN_H: R55.2, U6.4 (EN); also elsewhere on the board
BC_NPU_PWM0_M0: R45.1, R46.1, R47.1, R48.1; also elsewhere on the board
BC_VCC5V0_SYS: C69.1, C70.1, R72.2, U4.4 (IN), U5.4 (IN); also elsewhere on the board
BC_VCC5V0_SYS_P: C79.1, C80.1, C83.1, C86.1, L8.2, R58.1, R68.1, R71.1, R72.1
BC_VCC_3V3: R45.2, R47.2, R50.1, R52.1; also elsewhere on the board
BC_VCC_RTC: C78.1, U7.1 (OUT); also elsewhere on the board
BC_VCC_SYSIN: C67.1, C68.1, C71.1, C72.1, U6.5 (IN), U7.3 (IN)
BC_VDD_ARM: R69.2, R70.2; also elsewhere on the board
BC_VDD_NPU: C76.1, C81.1, C84.1, C87.1, R60.1, R61.1, R64.2, R69.1; also elsewhere on the board
BC_VDD_NPU_P: L6.2, R60.2, R64.1
BC_VDD_VEPU: C77.1, C82.1, C85.1, C88.1, R62.1, R63.1, R66.2, R70.1; also elsewhere on the board
BC_VDD_VEPU_P: L7.2, R62.2, R66.1
GND: C67.2, C68.2, C69.2, C70.2, C71.2, C72.2, C73.2, C74.2, C78.2, C80.2, C81.2, C82.2, C83.2, C84.2, C85.2, C86.2, C87.2, C88.2, D1.1 (K), R49.1, R51.1, R53.2, R54.2, R55.1, R59.2, R65.2, R67.2, R71.2, U4.2 (GND), U5.2 (GND), U6.2 (GND), U7.2 (GND); also elsewhere on the board
unnamed: C73.1, R46.2, R53.1, R56.1
unnamed: C74.1, R48.2, R54.1, R57.1
unnamed: C75.1, L8.1, U6.6 (LX)
unnamed: C75.2, U6.1 (BS)
unnamed: C76.2, R56.2, R61.2, R65.1, U4.5 (FB/OUT)
unnamed: C77.2, R57.2, R63.2, R67.1, U5.5 (FB/OUT)
unnamed: C79.2, R58.2, R59.1, U6.3 (FB/OUT)
unnamed: D1.2 (A), R68.2
unnamed: L6.1, U4.3 (LX)
unnamed: L7.1, U5.3 (LX)
unnamed: R49.2, R50.2, U4.1 (EN)
unnamed: R51.2, R52.2, U5.1 (EN)

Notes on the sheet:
FB loop

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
